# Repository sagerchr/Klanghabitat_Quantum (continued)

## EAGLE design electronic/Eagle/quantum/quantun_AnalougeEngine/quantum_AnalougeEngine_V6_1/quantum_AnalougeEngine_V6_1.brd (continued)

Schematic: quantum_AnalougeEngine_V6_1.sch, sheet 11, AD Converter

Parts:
C41, C115, C116: 10 uF; C1206
C42, C51, C52, C114: 100 nF; C0603
C117, C118: 1 uF; C0603
IC17: AD7606BSTZ-6; QFP50P1200X1200X160-64N
R14, R35, R96: 10 k; R0603

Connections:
+5V: C114.1, IC17.23 (VDRIVE), R35.2, R96.1; also elsewhere on the board
+5V(ANALOG): C41.1, C42.1, C51.1, C52.1, IC17.1 (AVCC_1), IC17.37 (AVCC_2), IC17.38 (AVCC_3), IC17.48 (AVCC_4); also elsewhere on the board
AGND: C41.2, C42.2, C51.2, C52.2, C114.2, C115.2, C116.2, C117.2, C118.2, IC17.2 (AGND_1), IC17.26 (AGND_2), IC17.35 (AGND_3), IC17.40 (AGND_4), IC17.41 (AGND_5), IC17.43 (REFGND_1), IC17.46 (REFGND_2), IC17.47 (AGND_6), IC17.50 (V1GND), IC17.52 (V2GND), IC17.54 (V3GND), IC17.55 (AGND_7), IC17.56 (AGND_8), IC17.58 (V4GND), IC17.60 (V5GND), IC17.62 (V6GND), IC17.63 (AGND_9), IC17.64 (AGND_10), R14.2; also elsewhere on the board
BUSY: IC17.14 (BUSY); also elsewhere on the board
CS: IC17.13 (!CS); also elsewhere on the board
CV_A_B: IC17.9 (CONVST_A), IC17.10 (CONVST_B); also elsewhere on the board
DB0: IC17.16 (DB0); also elsewhere on the board
DB1: IC17.17 (DB1); also elsewhere on the board
DB2: IC17.18 (DB2); also elsewhere on the board
DB3: IC17.19 (DB3); also elsewhere on the board
DB4: IC17.20 (DB4); also elsewhere on the board
DB5: IC17.21 (DB5); also elsewhere on the board
DB6: IC17.22 (DB6); also elsewhere on the board
DB7: IC17.24 (DB7/DOUTA); also elsewhere on the board
DB8: IC17.25 (DB8/DOUTB); also elsewhere on the board
DB9: IC17.27 (DB9); also elsewhere on the board
DB10: IC17.28 (DB10); also elsewhere on the board
DB11: IC17.29 (DB11); also elsewhere on the board
DB12: IC17.30 (DB12); also elsewhere on the board
DB13: IC17.31 (DB13); also elsewhere on the board
DB14: IC17.32 (DB14/HBEN); also elsewhere on the board
DB15: IC17.33 (DB15/BYTE_SEL); also elsewhere on the board
FRST: IC17.15 (FRSTDATA); also elsewhere on the board
L/M_IN(VCA1_IN): IC17.49 (V1); also elsewhere on the board
L/M_OUT(OUT_STAGE_LEFT)_BEFORE: IC17.59 (V5)
L/M_OUT(VCA1_OUT): IC17.53 (V3); also elsewhere on the board
unnamed: IC17.34 (REF_SELECT), R96.2
unnamed: IC17.6 (!PAR!/SER/BYTE_SEL), R14.1
unnamed: IC17.7 (!STBY), R35.1
unnamed: C115.1, IC17.42 (REFIN/REFOUT)
unnamed: C116.1, IC17.44 (REFCAPA), IC17.45 (REFCAPB)
unnamed: C117.1, IC17.36 (REGCAP_1)
unnamed: C118.1, IC17.39 (REGCAP_2)
OS0: IC17.3 (OS_0); also elsewhere on the board
OS1: IC17.4 (OS_1); also elsewhere on the board
OS2: IC17.5 (OS_2); also elsewhere on the board
R/S_IN(VCA2_IN): IC17.51 (V2); also elsewhere on the board
R/S_OUT(OUT_STAGE_RIGHT)_BEFORE: IC17.61 (V6)
R/S_OUT(VCA2_OUT): IC17.57 (V4); also elsewhere on the board
RANGE: IC17.8 (RANGE); also elsewhere on the board
RD: IC17.12 (!RD!/SCLK); also elsewhere on the board
RESET: IC17.11 (RESET); also elsewhere on the board

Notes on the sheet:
AD Converter
Analog Section

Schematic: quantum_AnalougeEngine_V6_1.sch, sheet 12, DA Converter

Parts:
C14, C24: 100 nF; C0603
C33, C34: 10 uF; C1206
IC2: DAC084S085CIMM_NOPB; SOP50P490X110-10N
R38, R41: 27 k; R0603
R40, R43: 160 k; R0603
R47, R76: 1k8; R0603
R74, R75: 10 k; R0603
R92, R93, R94: 500 R; R0603
TP03, TP04: TPTHT; THT_PIN

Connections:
+5V(ANALOG): C14.1, C24.1, C33.1, C34.1, IC2.1 (VA), IC2.7 (VREFIN); also elsewhere on the board
AGND: C14.2, C24.2, C33.2, C34.2, IC2.6 (GND), R47.1, R76.1; also elsewhere on the board
CS_DAC1: R94.2; also elsewhere on the board
DAC2_OUT1(OFFSET_VCA1): R74.2, R76.2; also elsewhere on the board
DAC2_OUT2(OFFSET_VCA2): R47.2, R75.2; also elsewhere on the board
DIN_DAC: R93.2, TP04.P$1; also elsewhere on the board
unnamed: IC2.5 (VOUTD), R75.1
unnamed: IC2.4 (VOUTC), R74.1
unnamed: IC2.2 (VOUTA), R38.2
unnamed: IC2.3 (VOUTB), R41.2
unnamed: IC2.10 (SCLK), R92.1
unnamed: IC2.8 (DIN), R93.1
unnamed: IC2.9 (!SYNC), R94.1
SCLK_DAC: R92.2, TP03.P$1; also elsewhere on the board
SYM1: R38.1, R40.2; also elsewhere on the board
SYM2: R41.1, R43.2; also elsewhere on the board
V-: R40.1, R43.1; also elsewhere on the board

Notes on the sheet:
DA Converter
could offset the main VCA by 153 mV which means about + 25,5 dB! step size is approx. 0.1dB per bit
main VCA offset
SYM THD VCAs

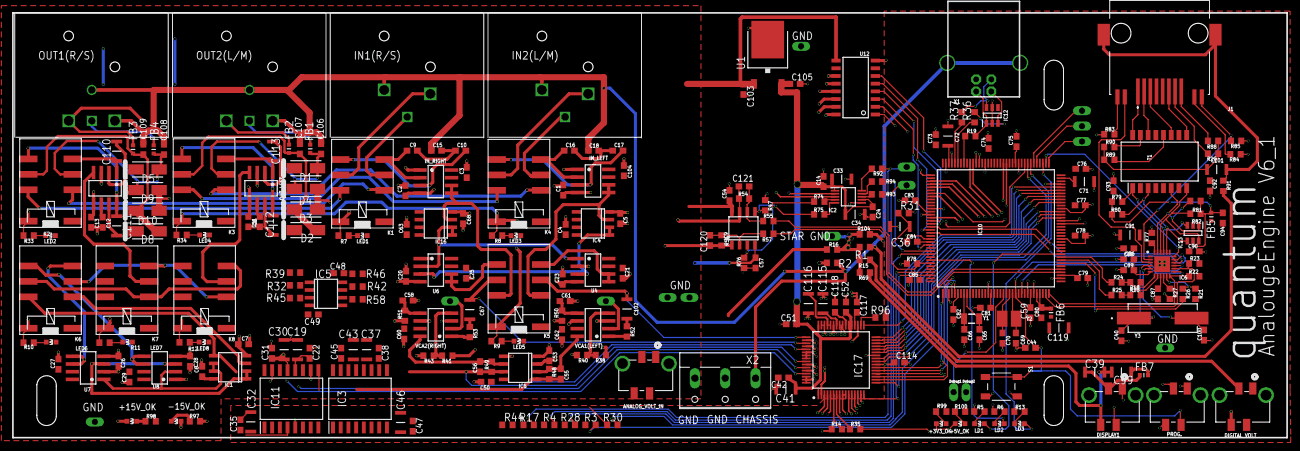
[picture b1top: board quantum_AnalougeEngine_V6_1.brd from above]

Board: 4 copper layers, 210.0 x 70.0 mm, 295 parts (0 on the bottom side), 229 nets.

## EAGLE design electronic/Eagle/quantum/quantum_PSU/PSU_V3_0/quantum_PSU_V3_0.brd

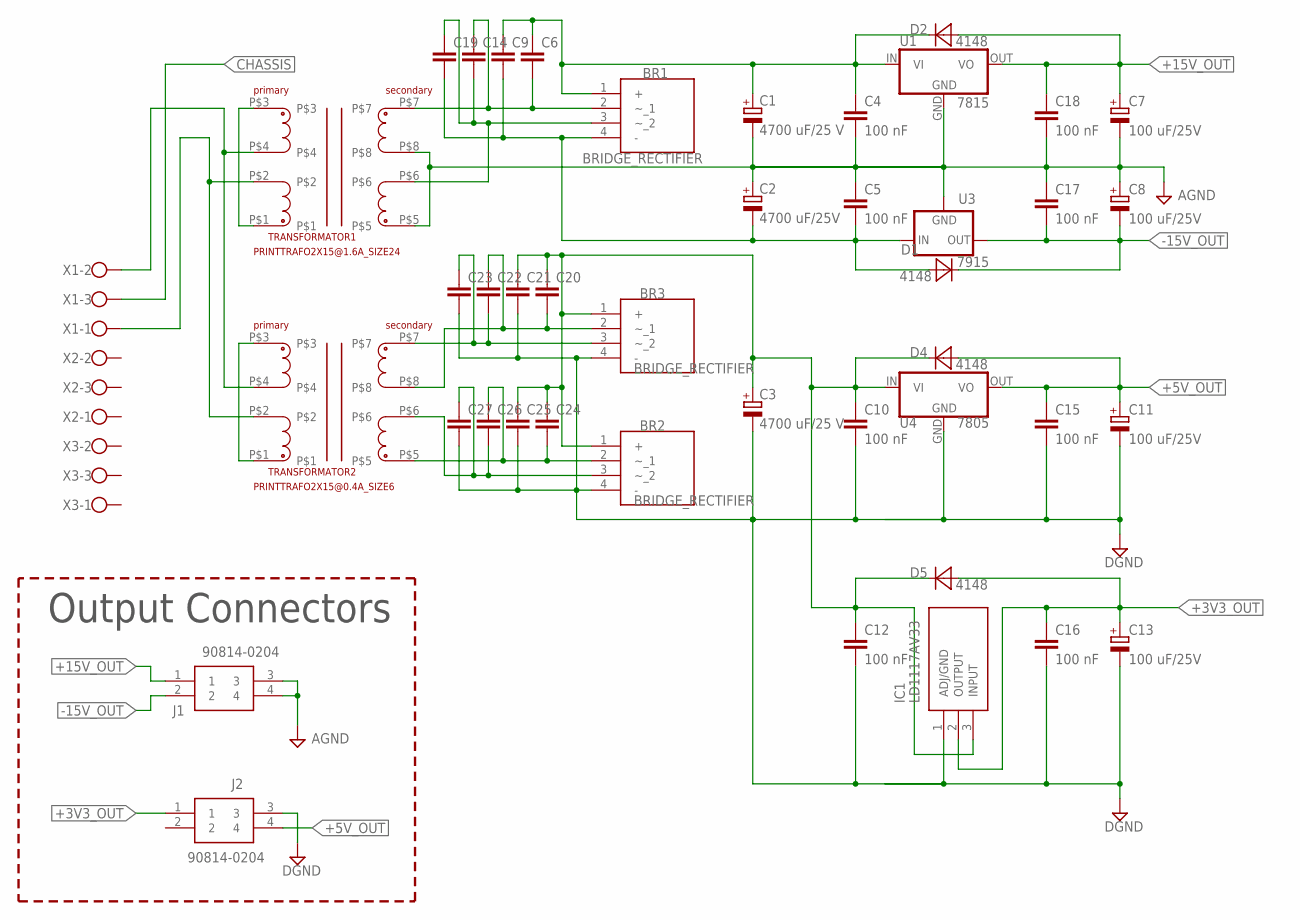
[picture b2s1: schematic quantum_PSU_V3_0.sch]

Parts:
BR1, BR2, BR3: BRIDGE_RECTIFIER; KBP308G
C1, C3: 4700 uF/25 V; ELECTROLYTIC_16MM
C2: 4700 uF/25V; ELECTROLYTIC_16MM
C4, C5, C10, C12, C15, C16, C17, C18: 100 nF; C5MM
C6, C9, C14, C19, C20, C21, C22, C23, C24, C25, C26, C27: CAPACITOR_2.5MM; C2.5MM
C7, C8, C11, C13: 100 uF/25V; ELECTROLYTIC_8MM
D1, D2, D4, D5: 4148; DIODE_THT_STANDING
IC1: LD1117AV33; TO255P460X1020X2008-3P
J1, J2: 90814-0204; MOLEX_90814-0204
TRANSFORMATOR1: PRINTTRAFO2X15@1.6A_SIZE24; LP_SIZE_24
TRANSFORMATOR2: PRINTTRAFO2X15@0.4A_SIZE6; LP_SIZE_6
U1: 7815; 78XXS_
U3: 7915; 79XXS
U4: 7805; 78XXS_
X1, X2, X3: CONNECTOR_3POL; W237-103

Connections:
+3V3_OUT: C13.+, C16.1, D5.A, IC1.2 (OUTPUT), J2.1
+5V_OUT: C11.+, C15.1, D4.A, J2.4, U4.OUT (VO)
+15V_OUT: C7.+, C18.1, D2.A, J1.1, U1.OUT (VO)
-15V_OUT: C8.-, C17.2, D1.C, J1.2, U3.OUT
AGND: C1.-, C2.+, C4.2, C5.1, C7.-, C8.+, C17.1, C18.2, J1.3, J1.4, TRANSFORMATOR1.P$5, TRANSFORMATOR1.P$8, U1.GND, U3.GND
CHASSIS: X1.3
DGND: BR2.4 (-), BR3.4 (-), C3.-, C10.2, C11.-, C12.2, C13.-, C15.2, C16.2, C21.2, C23.2, C25.2, C27.2, IC1.1 (ADJ/GND), J2.3, U4.GND
unnamed: BR3.3 (~_2), C22.2, C23.1, TRANSFORMATOR2.P$7
unnamed: TRANSFORMATOR2.P$1, TRANSFORMATOR2.P$3
unnamed: BR1.3 (~_2), C14.2, C19.1, TRANSFORMATOR1.P$6
unnamed: TRANSFORMATOR1.P$1, TRANSFORMATOR1.P$3
unnamed: BR3.2 (~_1), C20.2, C22.1, TRANSFORMATOR2.P$8
unnamed: BR2.3 (~_2), C26.2, C27.1, TRANSFORMATOR2.P$6
unnamed: TRANSFORMATOR1.P$4, TRANSFORMATOR2.P$4, X1.2
unnamed: TRANSFORMATOR1.P$2, TRANSFORMATOR2.P$2, X1.1
unnamed: BR2.1 (+), BR3.1 (+), C3.+, C10.1, C12.1, C20.1, C21.1, C24.1, C25.1, D4.C, D5.C, IC1.3 (INPUT), U4.IN (VI)
unnamed: BR1.2 (~_1), C6.2, C14.1, TRANSFORMATOR1.P$7
unnamed: BR2.2 (~_1), C24.2, C26.1, TRANSFORMATOR2.P$5
unnamed: BR1.1 (+), C1.+, C4.1, C6.1, C9.1, D2.C, U1.IN (VI)
unnamed: BR1.4 (-), C2.-, C5.2, C9.2, C19.2, D1.A, U3.IN

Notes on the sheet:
Output Connectors

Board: 2 copper layers, 45 parts (0 on the bottom side), 19 nets, no tracks yet.

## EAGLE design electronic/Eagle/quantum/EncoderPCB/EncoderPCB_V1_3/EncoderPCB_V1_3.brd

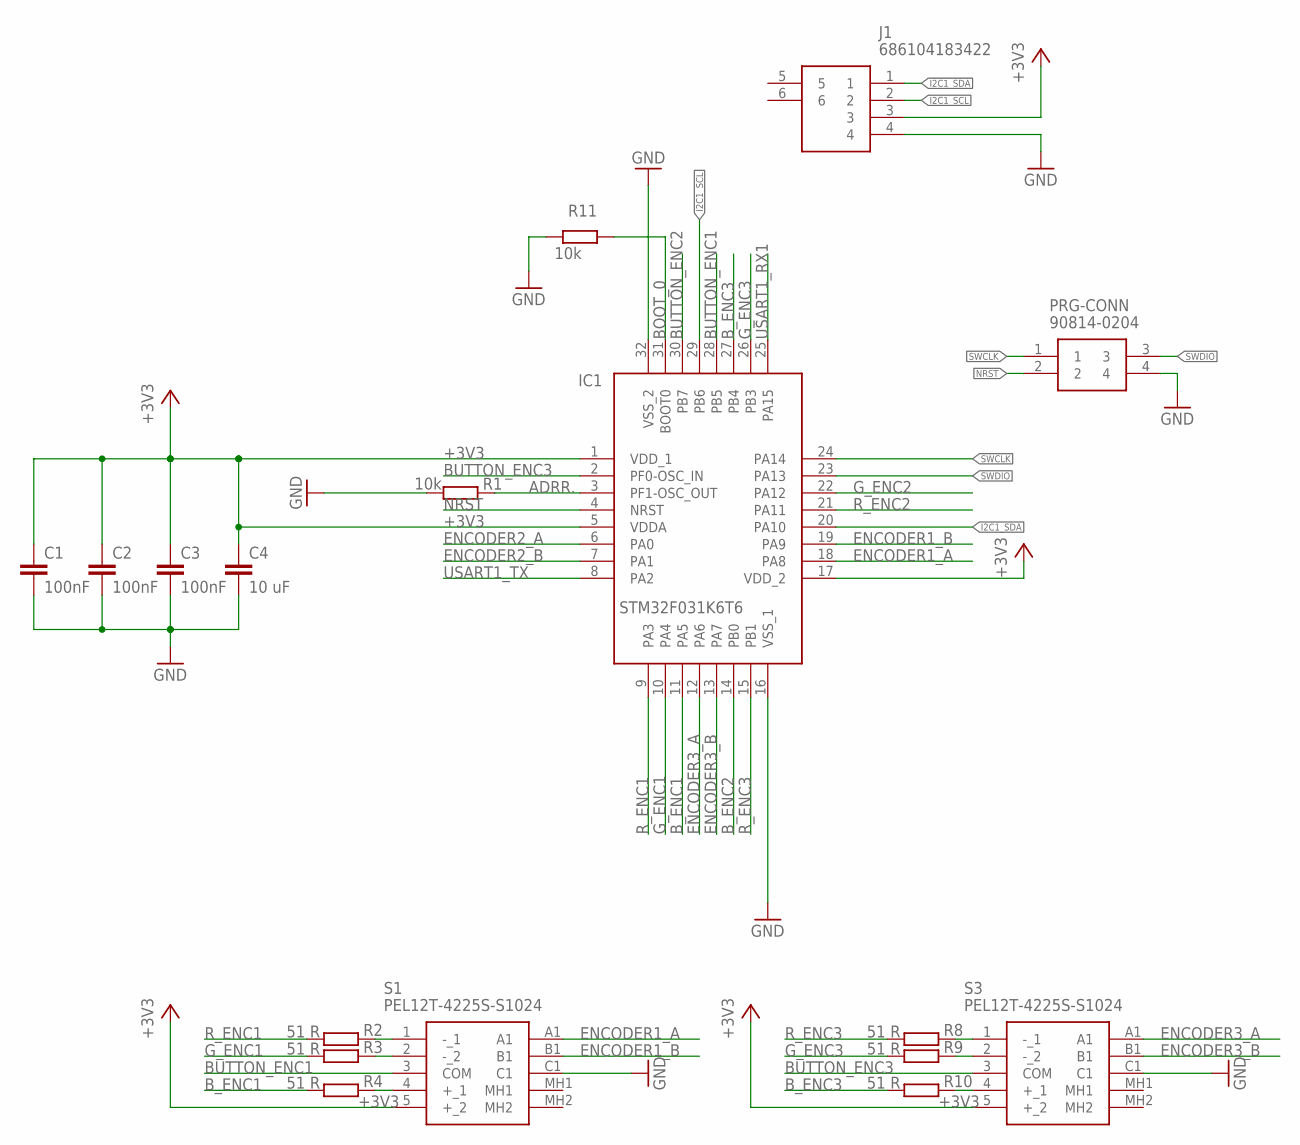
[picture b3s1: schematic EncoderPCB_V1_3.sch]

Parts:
C1, C2, C3: 100nF; C0603
C4: 10 uF; C1206
IC1: STM32F031K6T6; QFP80P900X900X160-32N
J1: 686104183422
PRG-CONN: 90814-0204; MOLEX_90814-0204
R1, R11: 10k; R0603
R2, R3, R4, R8, R9, R10: 51 R; R0603
S1, S3: PEL12T-4225S-S1024; PEL12T4225SS1024

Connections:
+3V3: C1.1, C2.1, C3.1, C4.1, IC1.1 (VDD_1), IC1.5 (VDDA), IC1.17 (VDD_2), J1.3, S1.5 (+_2), S3.5 (+_2)
ADRR.: IC1.3 (PF1-OSC_OUT), R1.2
BOOT_0: IC1.31 (BOOT0), R11.2
BUTTON_ENC1: IC1.28 (PB5), S1.3 (COM)
BUTTON_ENC2: IC1.30 (PB7)
BUTTON_ENC3: IC1.2 (PF0-OSC_IN), S3.3 (COM)
B_ENC1: IC1.11 (PA5), R4.1
B_ENC2: IC1.14 (PB0)
B_ENC3: IC1.27 (PB4), R10.1
ENCODER1_A: IC1.18 (PA8), S1.A1
ENCODER1_B: IC1.19 (PA9), S1.B1
ENCODER2_A: IC1.6 (PA0)
ENCODER2_B: IC1.7 (PA1)
ENCODER3_A: IC1.12 (PA6), S3.A1
ENCODER3_B: IC1.13 (PA7), S3.B1
GND: C1.2, C2.2, C3.2, C4.2, IC1.16 (VSS_1), IC1.32 (VSS_2), J1.4, PRG-CONN.4, R1.1, R11.1, S1.C1, S3.C1
G_ENC1: IC1.10 (PA4), R3.1
G_ENC2: IC1.22 (PA12)
G_ENC3: IC1.26 (PB3), R9.1
I2C1_SCL: IC1.29 (PB6), J1.2
I2C1_SDA: IC1.20 (PA10), J1.1
unnamed: R2.2, S1.1 (-_1)
unnamed: R3.2, S1.2 (-_2)
unnamed: R4.2, S1.4 (+_1)
unnamed: R8.2, S3.1 (-_1)
unnamed: R9.2, S3.2 (-_2)
unnamed: R10.2, S3.4 (+_1)
NRST: IC1.4 (NRST), PRG-CONN.2
R_ENC1: IC1.9 (PA3), R2.1
R_ENC2: IC1.21 (PA11)
R_ENC3: IC1.15 (PB1), R8.1
SWCLK: IC1.24 (PA14), PRG-CONN.1
SWDIO: IC1.23 (PA13), PRG-CONN.3
USART1_RX1: IC1.25 (PA15)
USART1_TX: IC1.8 (PA2)

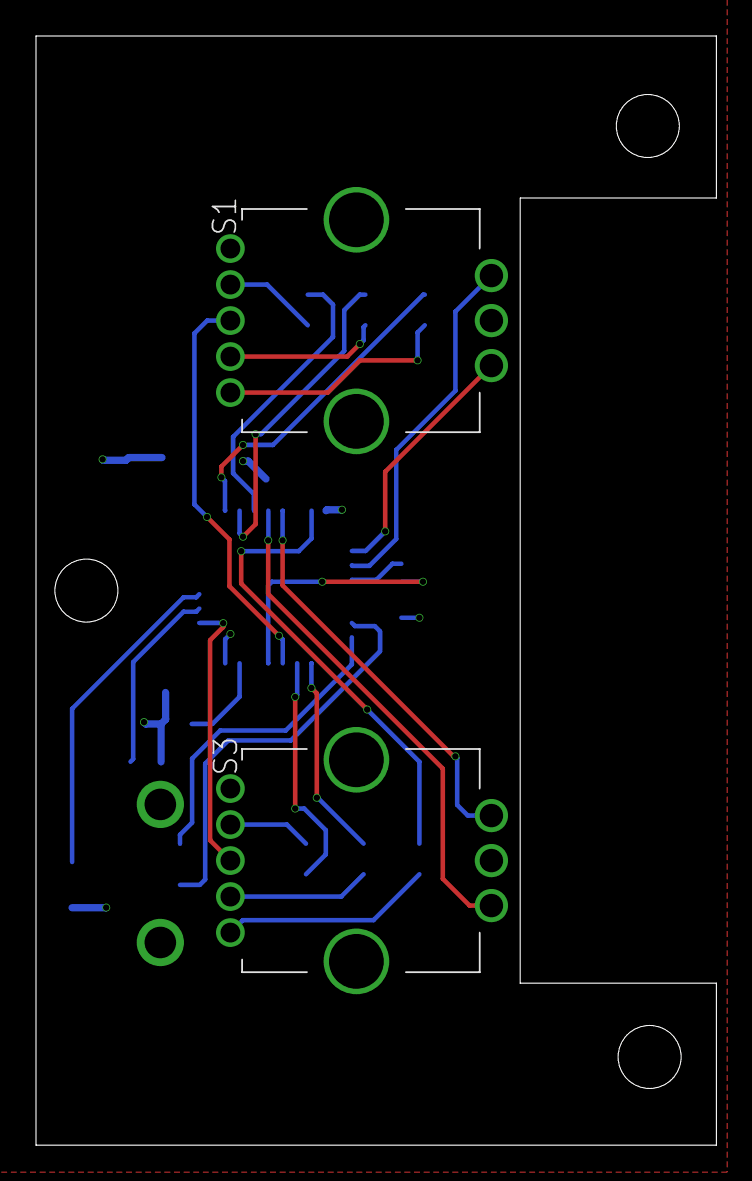
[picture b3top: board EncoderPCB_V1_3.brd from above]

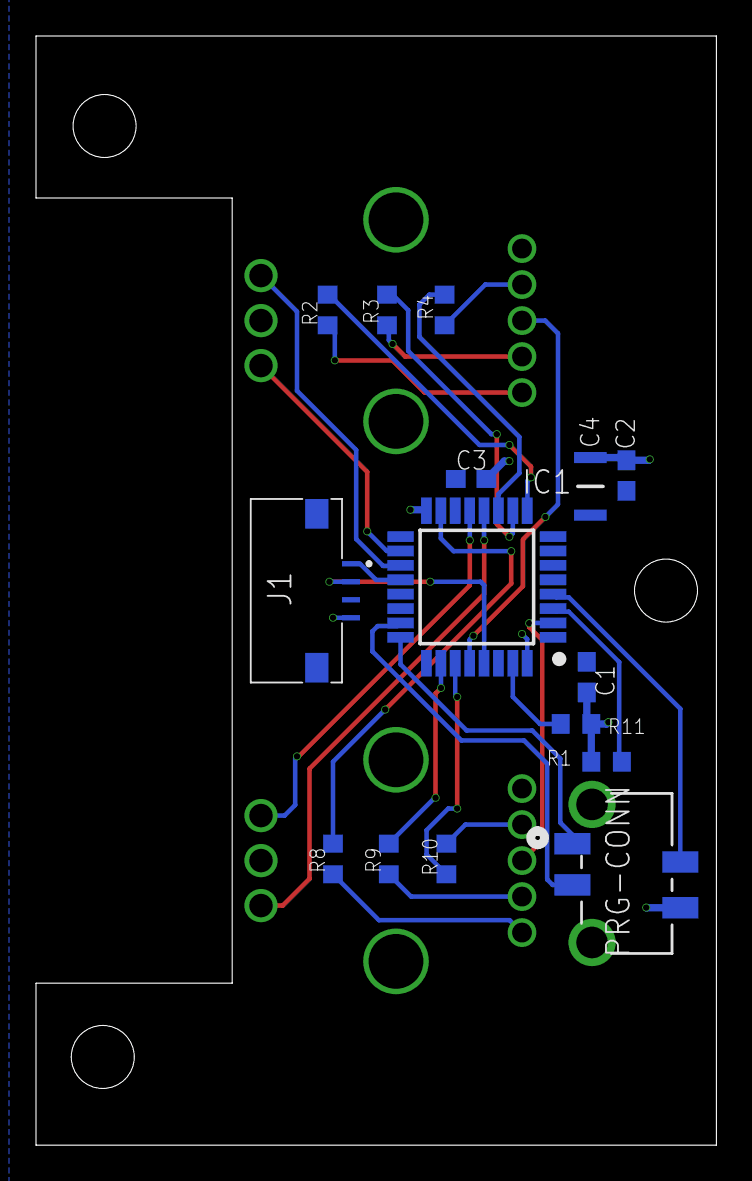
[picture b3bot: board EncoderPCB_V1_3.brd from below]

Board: 2 copper layers, 37.8 x 61.6 mm, 17 parts (15 on the bottom side), 27 nets.

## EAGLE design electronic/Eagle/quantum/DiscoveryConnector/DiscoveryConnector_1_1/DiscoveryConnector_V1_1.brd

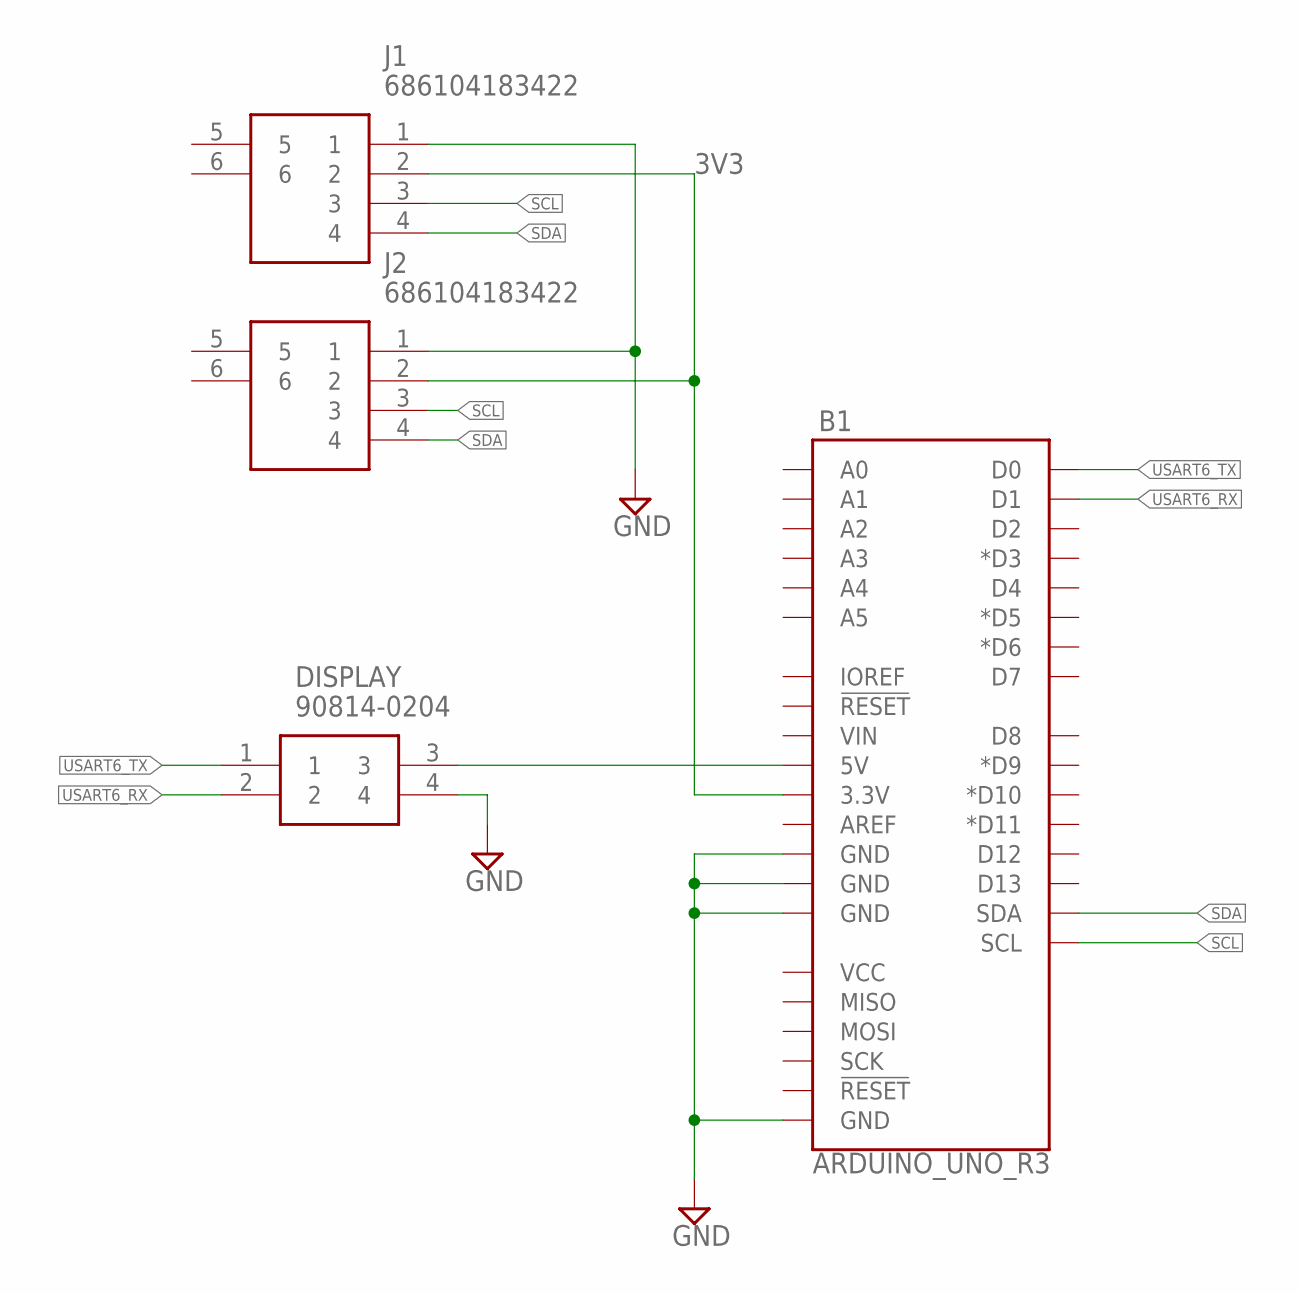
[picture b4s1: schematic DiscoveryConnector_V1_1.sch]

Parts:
B1: ARDUINO_UNO_R3; ARDUINO_R3
DISPLAY: 90814-0204; MOLEX_90814-0204
J1, J2: 686104183422

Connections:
3V3: B1.3.3V, J1.2, J2.2
GND: B1.GND@1 (GND), B1.GND@2 (GND), B1.GND@3 (GND), B1.GND@4 (GND), DISPLAY.4, J1.1, J2.1
unnamed: B1.5V, DISPLAY.3
SCL: B1.SCL, J1.3, J2.3
SDA: B1.SDA, J1.4, J2.4
USART6_RX: B1.D1, DISPLAY.2
USART6_TX: B1.D0, DISPLAY.1

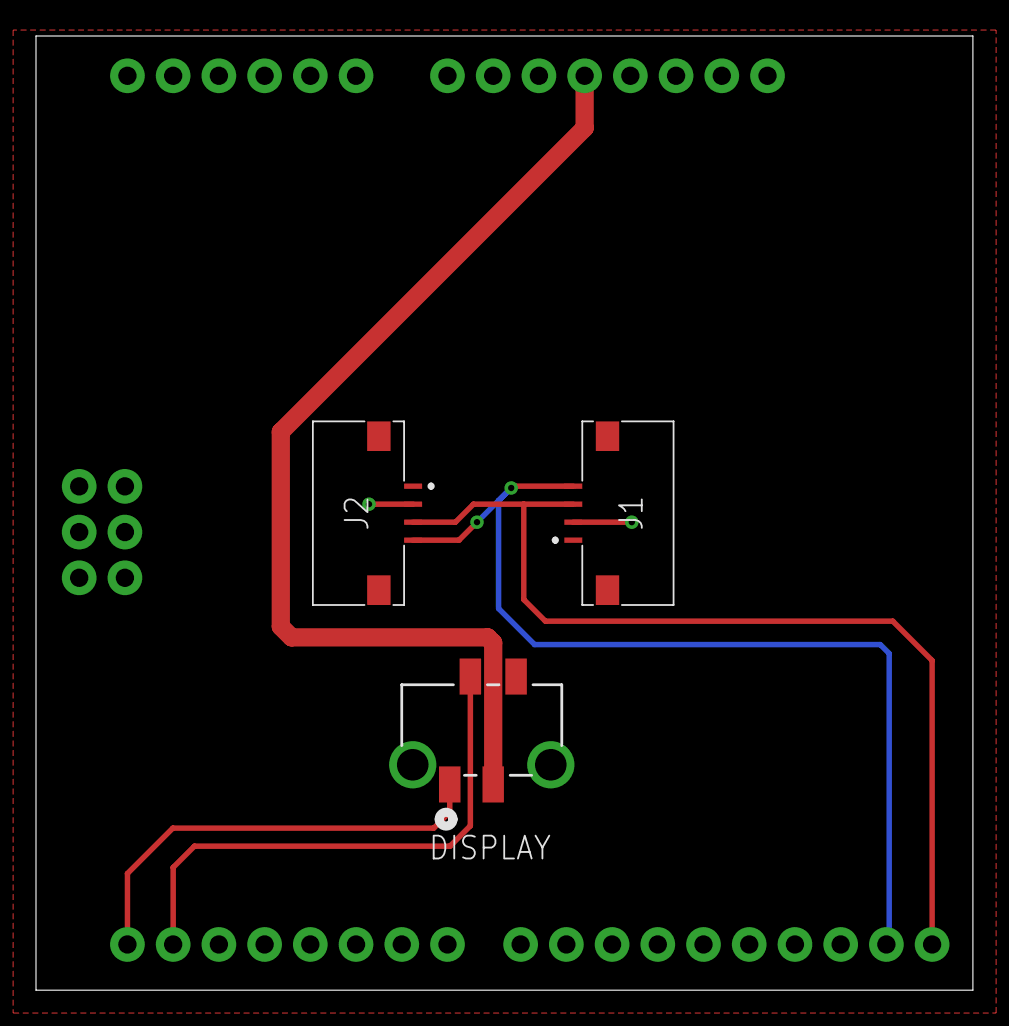
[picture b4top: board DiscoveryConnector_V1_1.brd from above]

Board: 2 copper layers, 52.0 x 53.0 mm, 4 parts (0 on the bottom side), 7 nets.

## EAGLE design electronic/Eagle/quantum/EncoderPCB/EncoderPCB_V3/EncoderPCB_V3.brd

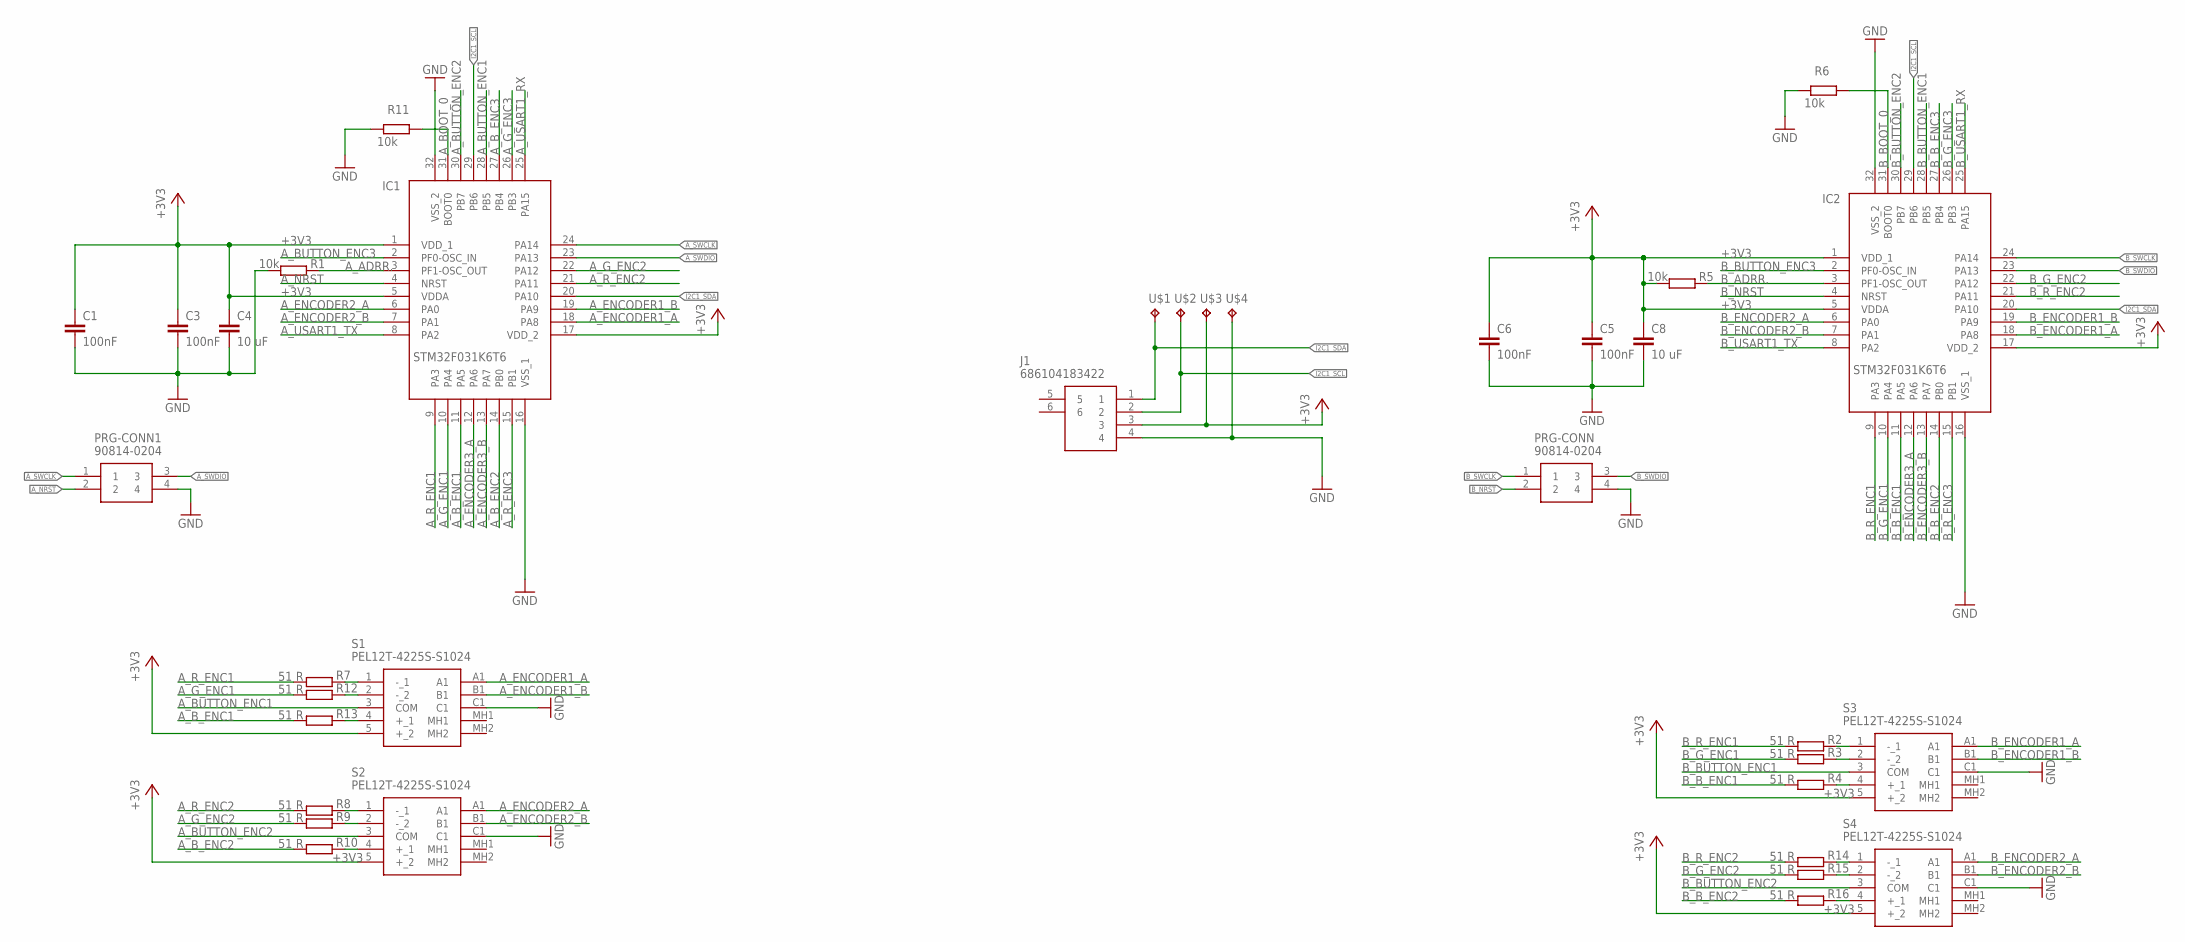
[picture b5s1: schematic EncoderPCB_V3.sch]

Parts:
C1, C3, C5, C6: 100nF; C0603
C4, C8: 10 uF; C1206
IC1, IC2: STM32F031K6T6; QFP80P900X900X160-32N
J1: 686104183422
PRG-CONN, PRG-CONN1: 90814-0204; MOLEX_90814-0204
R1, R5, R6, R11: 10k; R0603
R2, R3, R4, R7, R8, R9, R10, R12, R13, R14, R15, R16: 51 R; R0603
S1, S2, S3, S4: PEL12T-4225S-S1024; PEL12T4225SS1024
U$1, U$2, U$3, U$4: TP; OVAL_PAD

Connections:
+3V3: C1.1, C3.1, C4.1, C5.1, C6.1, C8.1, IC1.1 (VDD_1), IC1.5 (VDDA), IC1.17 (VDD_2), IC2.1 (VDD_1), IC2.5 (VDDA), IC2.17 (VDD_2), J1.3, R5.1, S1.5 (+_2), S2.5 (+_2), S3.5 (+_2), S4.5 (+_2), U$3.P$1
A_ADRR.: IC1.3 (PF1-OSC_OUT), R1.2
A_BOOT_0: IC1.31 (BOOT0), R11.2
A_BUTTON_ENC1: IC1.28 (PB5), S1.3 (COM)
A_BUTTON_ENC2: IC1.30 (PB7), S2.3 (COM)
A_BUTTON_ENC3: IC1.2 (PF0-OSC_IN)
A_B_ENC1: IC1.11 (PA5), R13.1
A_B_ENC2: IC1.14 (PB0), R10.1
A_B_ENC3: IC1.27 (PB4)
A_ENCODER1_A: IC1.18 (PA8), S1.A1
A_ENCODER1_B: IC1.19 (PA9), S1.B1
A_ENCODER2_A: IC1.6 (PA0), S2.A1
A_ENCODER2_B: IC1.7 (PA1), S2.B1
A_ENCODER3_A: IC1.12 (PA6)
A_ENCODER3_B: IC1.13 (PA7)
A_G_ENC1: IC1.10 (PA4), R12.1
A_G_ENC2: IC1.22 (PA12), R9.1
A_G_ENC3: IC1.26 (PB3)
A_NRST: IC1.4 (NRST), PRG-CONN1.2
A_R_ENC1: IC1.9 (PA3), R7.1
A_R_ENC2: IC1.21 (PA11), R8.1
A_R_ENC3: IC1.15 (PB1)
A_SWCLK: IC1.24 (PA14), PRG-CONN1.1
A_SWDIO: IC1.23 (PA13), PRG-CONN1.3
A_USART1_RX: IC1.25 (PA15)
A_USART1_TX: IC1.8 (PA2)
B_ADRR.: IC2.3 (PF1-OSC_OUT), R5.2
B_BOOT_0: IC2.31 (BOOT0), R6.2
B_BUTTON_ENC1: IC2.28 (PB5), S3.3 (COM)
B_BUTTON_ENC2: IC2.30 (PB7), S4.3 (COM)
B_BUTTON_ENC3: IC2.2 (PF0-OSC_IN)
B_B_ENC1: IC2.11 (PA5), R4.1
B_B_ENC2: IC2.14 (PB0), R16.1
B_B_ENC3: IC2.27 (PB4)
B_ENCODER1_A: IC2.18 (PA8), S3.A1
B_ENCODER1_B: IC2.19 (PA9), S3.B1
B_ENCODER2_A: IC2.6 (PA0), S4.A1
B_ENCODER2_B: IC2.7 (PA1), S4.B1
B_ENCODER3_A: IC2.12 (PA6)
B_ENCODER3_B: IC2.13 (PA7)
B_G_ENC1: IC2.10 (PA4), R3.1
B_G_ENC2: IC2.22 (PA12), R15.1
B_G_ENC3: IC2.26 (PB3)
B_NRST: IC2.4 (NRST), PRG-CONN.2
B_R_ENC1: IC2.9 (PA3), R2.1
B_R_ENC2: IC2.21 (PA11), R14.1
B_R_ENC3: IC2.15 (PB1)
B_SWCLK: IC2.24 (PA14), PRG-CONN.1
B_SWDIO: IC2.23 (PA13), PRG-CONN.3
B_USART1_RX: IC2.25 (PA15)
B_USART1_TX: IC2.8 (PA2)
GND: C1.2, C3.2, C4.2, C5.2, C6.2, C8.2, IC1.16 (VSS_1), IC1.32 (VSS_2), IC2.16 (VSS_1), IC2.32 (VSS_2), J1.4, PRG-CONN.4, PRG-CONN1.4, R1.1, R6.1, R11.1, S1.C1, S2.C1, S3.C1, S4.C1, U$4.P$1
I2C1_SCL: IC1.29 (PB6), IC2.29 (PB6), J1.2, U$2.P$1
I2C1_SDA: IC1.20 (PA10), IC2.20 (PA10), J1.1, U$1.P$1
unnamed: R7.2, S1.1 (-_1)
unnamed: R12.2, S1.2 (-_2)
unnamed: R13.2, S1.4 (+_1)
unnamed: R14.2, S4.1 (-_1)
unnamed: R15.2, S4.2 (-_2)
unnamed: R16.2, S4.4 (+_1)
unnamed: R2.2, S3.1 (-_1)
unnamed: R3.2, S3.2 (-_2)
unnamed: R4.2, S3.4 (+_1)
unnamed: R8.2, S2.1 (-_1)
unnamed: R9.2, S2.2 (-_2)
unnamed: R10.2, S2.4 (+_1)

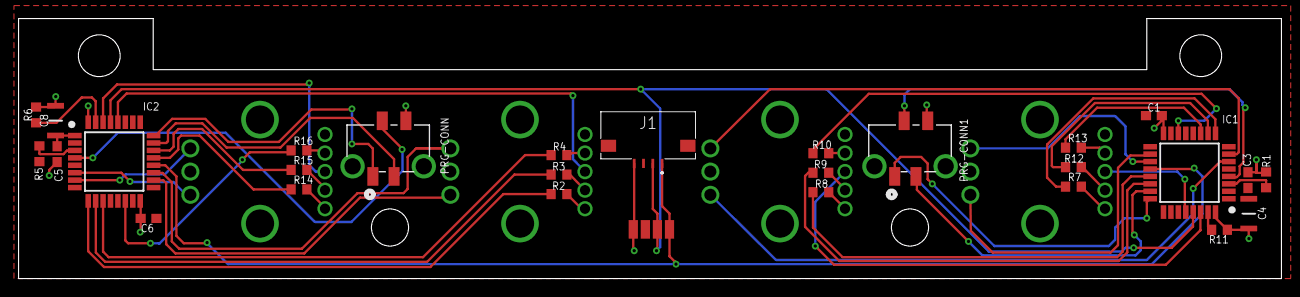
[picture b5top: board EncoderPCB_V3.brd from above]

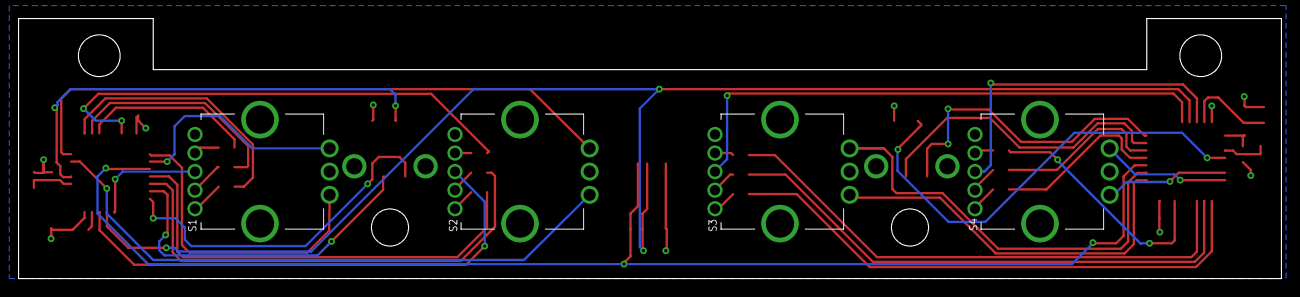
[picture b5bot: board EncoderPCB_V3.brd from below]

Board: 2 copper layers, 136.0 x 28.0 mm, 35 parts (4 on the bottom side), 50 nets.

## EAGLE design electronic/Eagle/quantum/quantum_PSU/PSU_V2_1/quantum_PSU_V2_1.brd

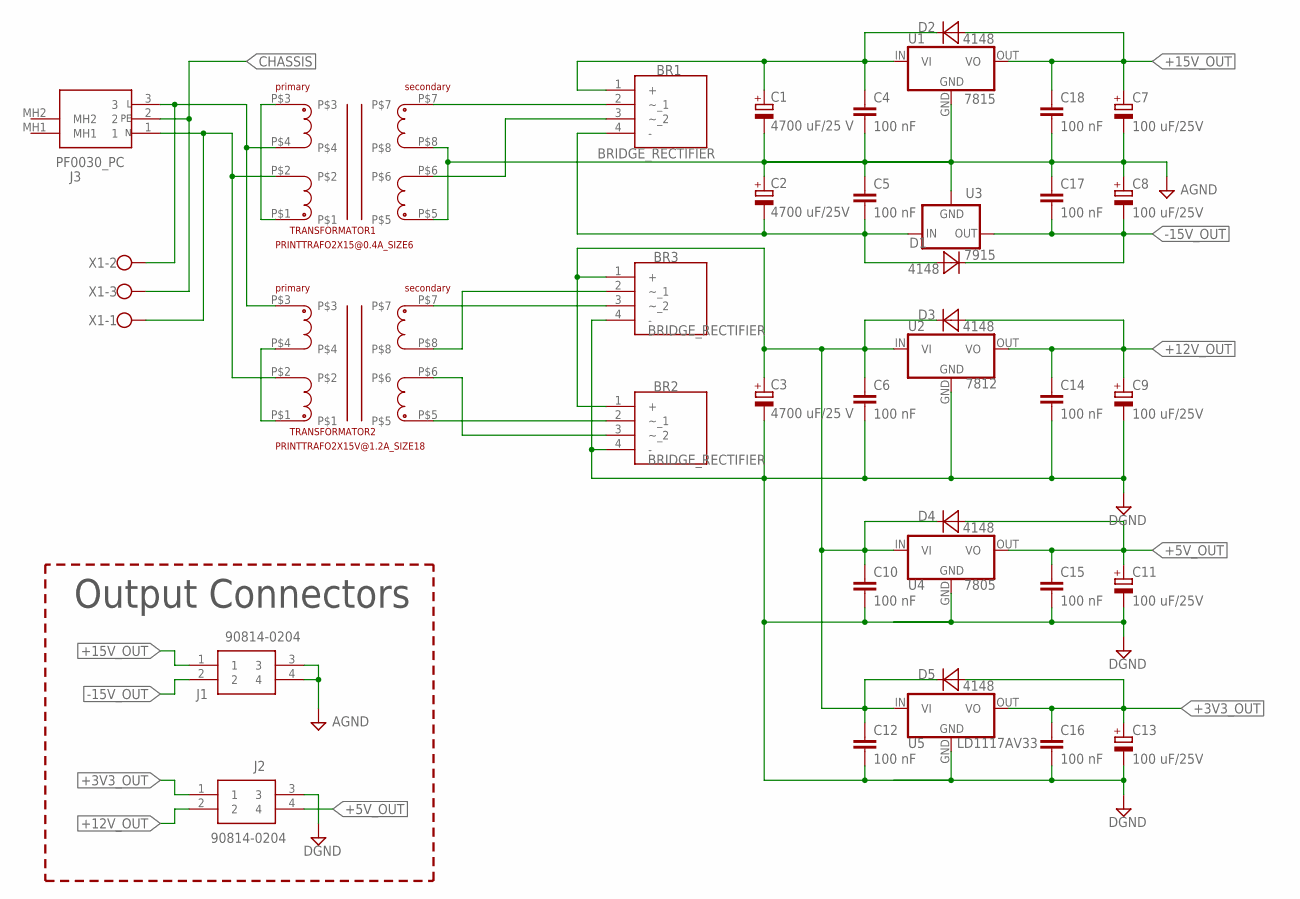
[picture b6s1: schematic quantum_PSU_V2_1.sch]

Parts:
BR1, BR2, BR3: BRIDGE_RECTIFIER; KBP308G
C1, C3: 4700 uF/25 V; ELECTROLYTIC_16MM
C2: 4700 uF/25V; ELECTROLYTIC_16MM
C4, C5, C6, C10, C12, C14, C15, C16, C17, C18: 100 nF; C5MM
C7, C8, C9, C11, C13: 100 uF/25V; ELECTROLYTIC_8MM
D1, D2, D3, D4, D5: 4148; DIODE_THT_STANDING
J1, J2: 90814-0204; MOLEX_90814-0204
J3: PF0030_PC; PF0030PC
TRANSFORMATOR1: PRINTTRAFO2X15@0.4A_SIZE6; LP_SIZE_6
TRANSFORMATOR2: PRINTTRAFO2X15V@1.2A_SIZE18; LPI_SIZE_18
U1: 7815; 78XXS_
U2: 7812; 78XXS_
U3: 7915; 79XXS
U4: 7805; 78XXS_
U5: LD1117AV33; 78XXS_
X1: CONNECTOR_3POL; W237-103

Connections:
+3V3_OUT: C13.+, C16.1, D5.A, J2.1, U5.OUT (VO)
+5V_OUT: C11.+, C15.1, D4.A, J2.4, U4.OUT (VO)
+12V_OUT: C9.+, C14.1, D3.A, J2.2, U2.OUT (VO)
+15V_OUT: C7.+, C18.1, D2.A, J1.1, U1.OUT (VO)
-15V_OUT: C8.-, C17.2, D1.C, J1.2, U3.OUT
AGND: C1.-, C2.+, C4.2, C5.1, C7.-, C8.+, C17.1, C18.2, J1.3, J1.4, TRANSFORMATOR1.P$5, TRANSFORMATOR1.P$8, U1.GND, U3.GND
CHASSIS: J3.2, X1.3
DGND: BR2.4 (-), BR3.4 (-), C3.-, C6.2, C9.-, C10.2, C11.-, C12.2, C13.-, C14.2, C15.2, C16.2, J2.3, U2.GND, U4.GND, U5.GND
unnamed: BR3.3 (~_2), TRANSFORMATOR2.P$7
unnamed: BR2.1 (+), BR3.1 (+), C3.+, C6.1, C10.1, C12.1, D3.C, D4.C, D5.C, U2.IN (VI), U4.IN (VI), U5.IN (VI)
unnamed: BR1.3 (~_2), TRANSFORMATOR1.P$6
unnamed: TRANSFORMATOR1.P$1, TRANSFORMATOR1.P$3
unnamed: TRANSFORMATOR2.P$1, TRANSFORMATOR2.P$4
unnamed: BR3.2 (~_1), TRANSFORMATOR2.P$8
unnamed: BR2.3 (~_2), TRANSFORMATOR2.P$6
unnamed: J3.3, TRANSFORMATOR1.P$4, TRANSFORMATOR2.P$3, X1.2
unnamed: J3.1, TRANSFORMATOR1.P$2, TRANSFORMATOR2.P$2, X1.1
unnamed: BR1.2 (~_1), TRANSFORMATOR1.P$7
unnamed: BR2.2 (~_1), TRANSFORMATOR2.P$5
unnamed: BR1.1 (+), C1.+, C4.1, D2.C, U1.IN (VI)
unnamed: BR1.4 (-), C2.-, C5.2, D1.A, U3.IN

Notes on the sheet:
Output Connectors

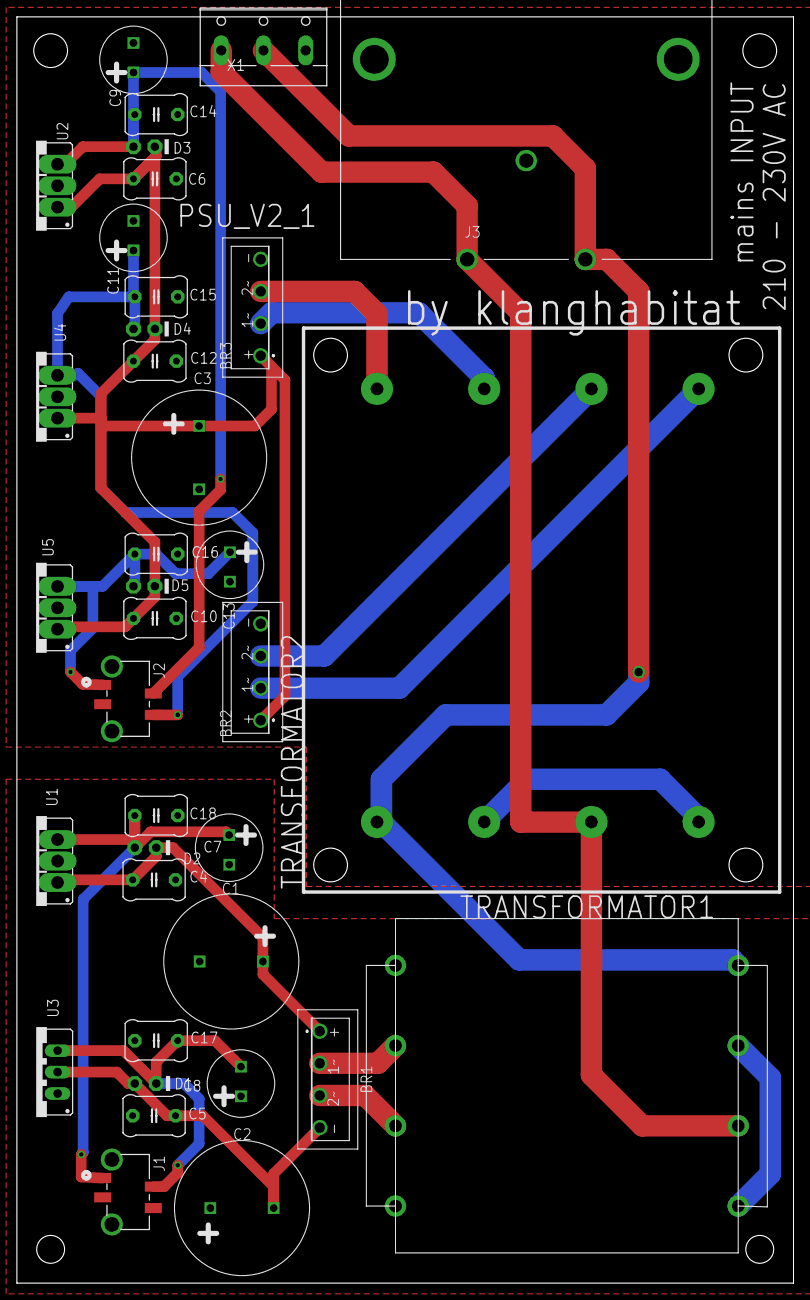
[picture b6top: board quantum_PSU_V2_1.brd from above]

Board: 2 copper layers, 92.0 x 150.0 mm, 37 parts (0 on the bottom side), 21 nets.
